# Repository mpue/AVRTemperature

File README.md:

AVRTemperature
==============================

Measuring temperature with the ATMega8 and a TSIC 0306. This version is interrupt driven.

Hardware: ATMega8/16MHz
 
This program measures the temperature of a TSIC0306 temperature sensor, which is
connected to the INT1 pin. The sensor itself is powered via the ZACPIN defined
in zacwire.h

At the beginning the TSIC is powered on and when the first falling edge occurs the measurement
starts. Timer 1 is started in normal mode. When the first rising edge occurs the timer is being
stopped and the value from the TCNT1 register is taken as strobe value.

From now on on each falling edge of the INT1 pin the timer1 is started in ctc mode. Each time
the OCR1A register is equal to the timer value, the TIMER1_COMPA_vect interrupt service routine
is being triggered. This is exactly the 50% duty cycle time which is needed to detect the state
of each bit.

After measuring the MSB the parity bit and the stop bit are being skipped, then the measurement
for the LSB continues, at the end the parity bit is skipped again and the measurement is complete.
The whole thing is driven by a "state machine" like mechanism. This in fact not a real state machine,
since we have no events, rules or transitions.
 
This code doesn't represent the most efficient solution. The goal was to understand the zacwire protocol
and to write human readable code. Feel free to improve the code and give suggestions.

Usage
==============================
You must have avrdude and avr-gcc installed. Use an ATMega8@16MHz, given the attached schematic.

Program with:

make program

You'll have to adjust your programmer before. Don't mess up the fuses!

Schematics and board layout resides in the eagle folder.

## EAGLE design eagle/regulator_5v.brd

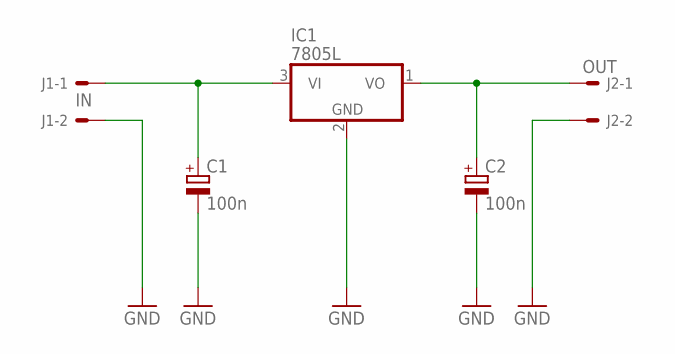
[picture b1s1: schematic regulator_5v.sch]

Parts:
C1, C2: 100n; TT2D5
IC1: 7805L; TO92
J1: IN; 6410-02
J2: OUT; 6410-02

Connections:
GND: C1.-, C2.-, IC1.2 (GND), J1.2, J2.2
unnamed: C1.+, IC1.3 (VI), J1.1
unnamed: C2.+, IC1.1 (VO), J2.1

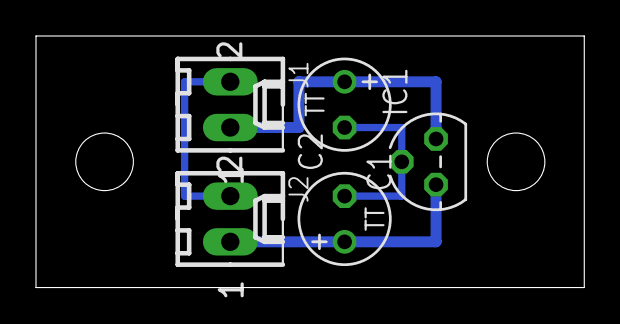
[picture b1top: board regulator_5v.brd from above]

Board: 2 copper layers, 30.5 x 14.0 mm, 5 parts (0 on the bottom side), 3 nets.

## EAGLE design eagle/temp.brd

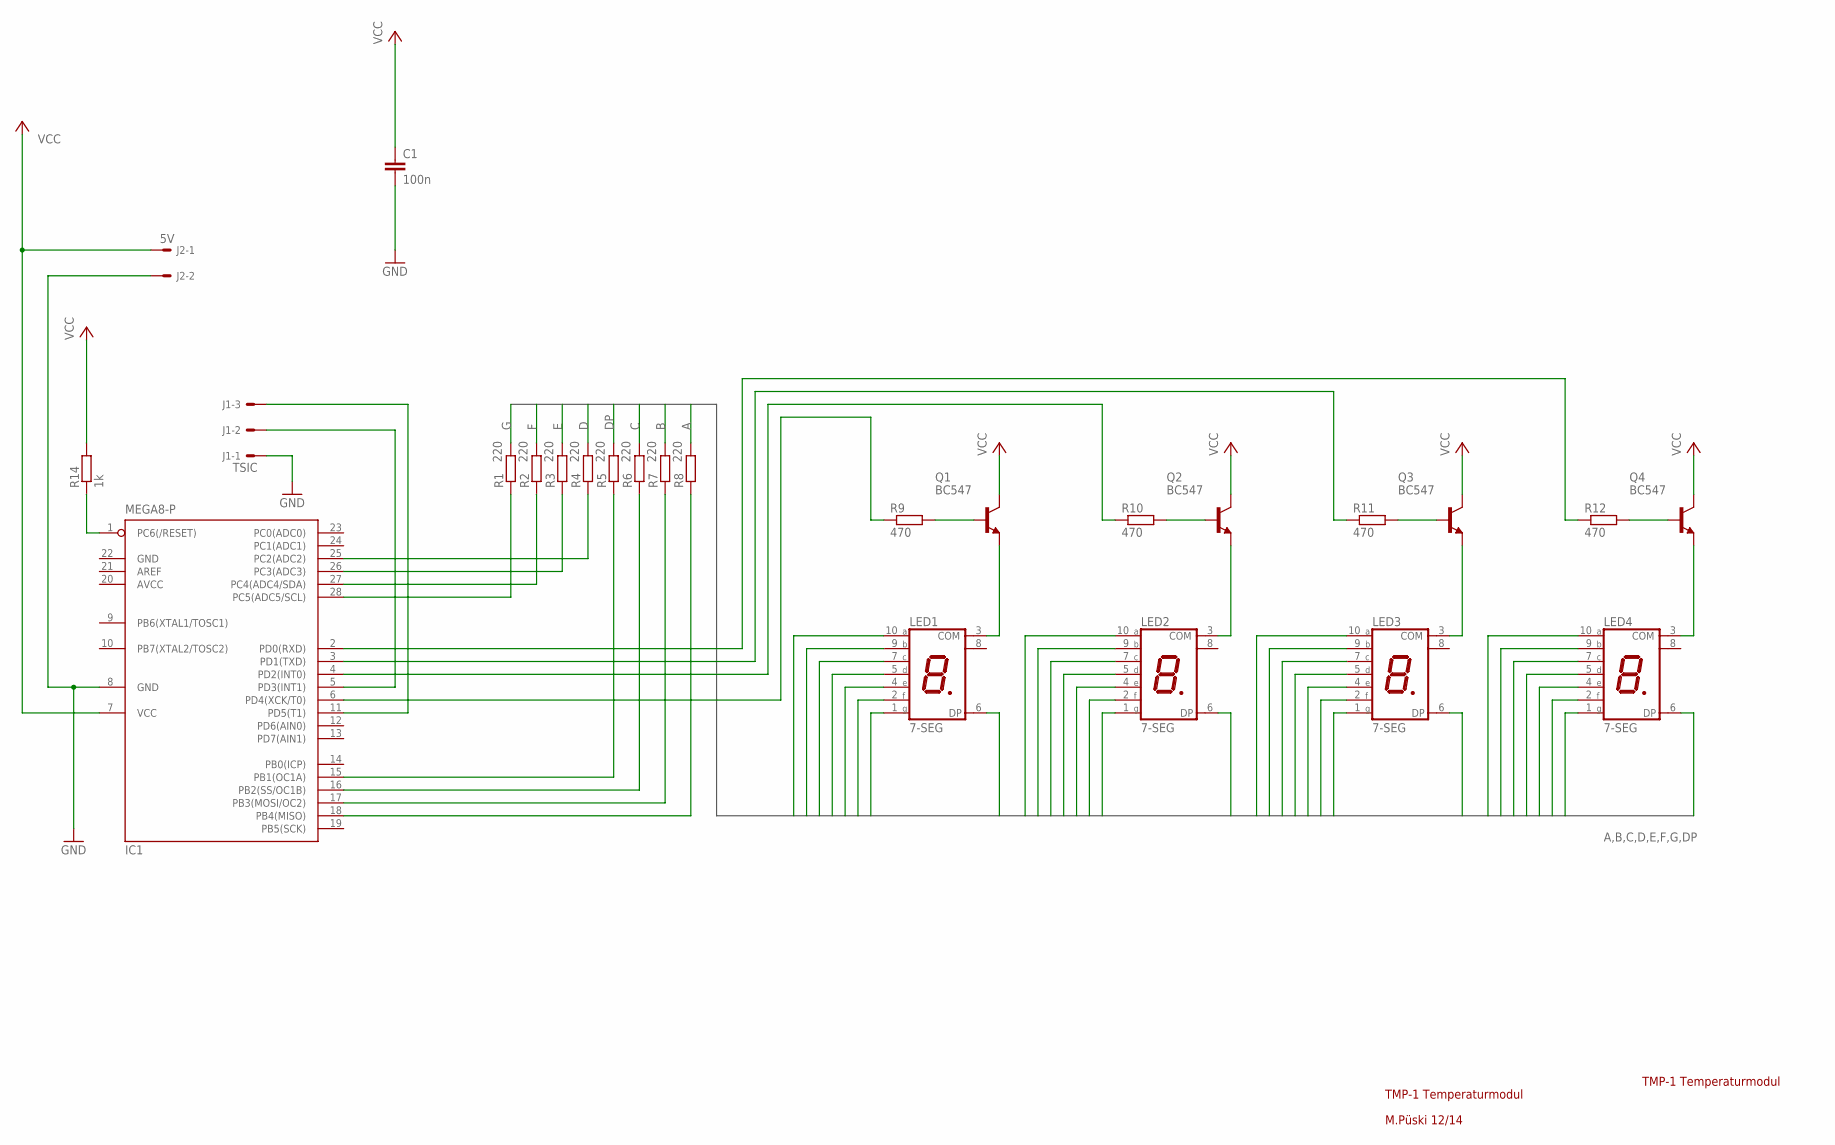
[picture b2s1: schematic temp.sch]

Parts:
C1: 100n; C050-024X044
IC1: MEGA8-P; DIL28-3
J1: TSIC; 6410-03
J2: 5V; 6410-02
LED1, LED2, LED3, LED4: 7-SEG; SA39-11SRWA
Q1, Q2, Q3, Q4: BC547; TO92
R1, R2, R4, R5, R6, R7, R8: 220; 0204/7
R3: 220; 0204V
R9, R10, R12: 470; 0204/7
R11: 470; 0204V
R14: 1k; 0204/7

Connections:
A: LED1.10 (A), LED2.10 (A), LED3.10 (A), LED4.10 (A), R8.2
AVCC: IC1.20 (AVCC)
B: LED1.9 (B), LED2.9 (B), LED3.9 (B), LED4.9 (B), R7.2
C: LED1.7 (C), LED2.7 (C), LED3.7 (C), LED4.7 (C), R6.2
D: LED1.5 (D), LED2.5 (D), LED3.5 (D), LED4.5 (D), R4.2
DP: LED1.6 (DP), LED2.6 (DP), LED3.6 (DP), LED4.6 (DP), R5.2
E: LED1.4 (E), LED2.4 (E), LED3.4 (E), LED4.4 (E), R3.2
F: LED1.2 (F), LED2.2 (F), LED3.2 (F), LED4.2 (F), R2.2
G: LED1.1 (G), LED2.1 (G), LED3.1 (G), LED4.1 (G), R1.2
GND: C1.2, IC1.8 (GND), IC1.22 (GND), J1.1, J2.2
unnamed: IC1.27 (PC4(ADC4/SDA)), R2.1
unnamed: IC1.26 (PC3(ADC3)), R3.1
unnamed: IC1.25 (PC2(ADC2)), R4.1
unnamed: IC1.15 (PB1(OC1A)), R5.1
unnamed: IC1.16 (PB2(SS/OC1B)), R6.1
unnamed: IC1.17 (PB3(MOSI/OC2)), R7.1
unnamed: IC1.18 (PB4(MISO)), R8.1
unnamed: Q1.2 (B), R9.2
unnamed: Q2.2 (B), R10.2
unnamed: Q3.2 (B), R11.2
unnamed: LED3.3 (COM), Q3.1 (E)
unnamed: LED2.3 (COM), Q2.1 (E)
unnamed: LED1.3 (COM), Q1.1 (E)
unnamed: IC1.2 (PD0(RXD)), R12.1
unnamed: IC1.3 (PD1(TXD)), R11.1
unnamed: IC1.4 (PD2(INT0)), R10.1
unnamed: IC1.28 (PC5(ADC5/SCL)), R1.1
unnamed: Q4.2 (B), R12.2
unnamed: LED4.3 (COM), Q4.1 (E)
unnamed: IC1.1 (PC6(/RESET)), R14.1
unnamed: IC1.6 (PD4(XCK/T0)), R9.1
unnamed: IC1.11 (PD5(T1)), J1.3
unnamed: IC1.5 (PD3(INT1)), J1.2
VCC: C1.1, IC1.7 (VCC), J2.1, Q1.3 (C), Q2.3 (C), Q3.3 (C), Q4.3 (C), R14.2

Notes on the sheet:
TMP-1 Temperaturmodul
M.Püski 12/14

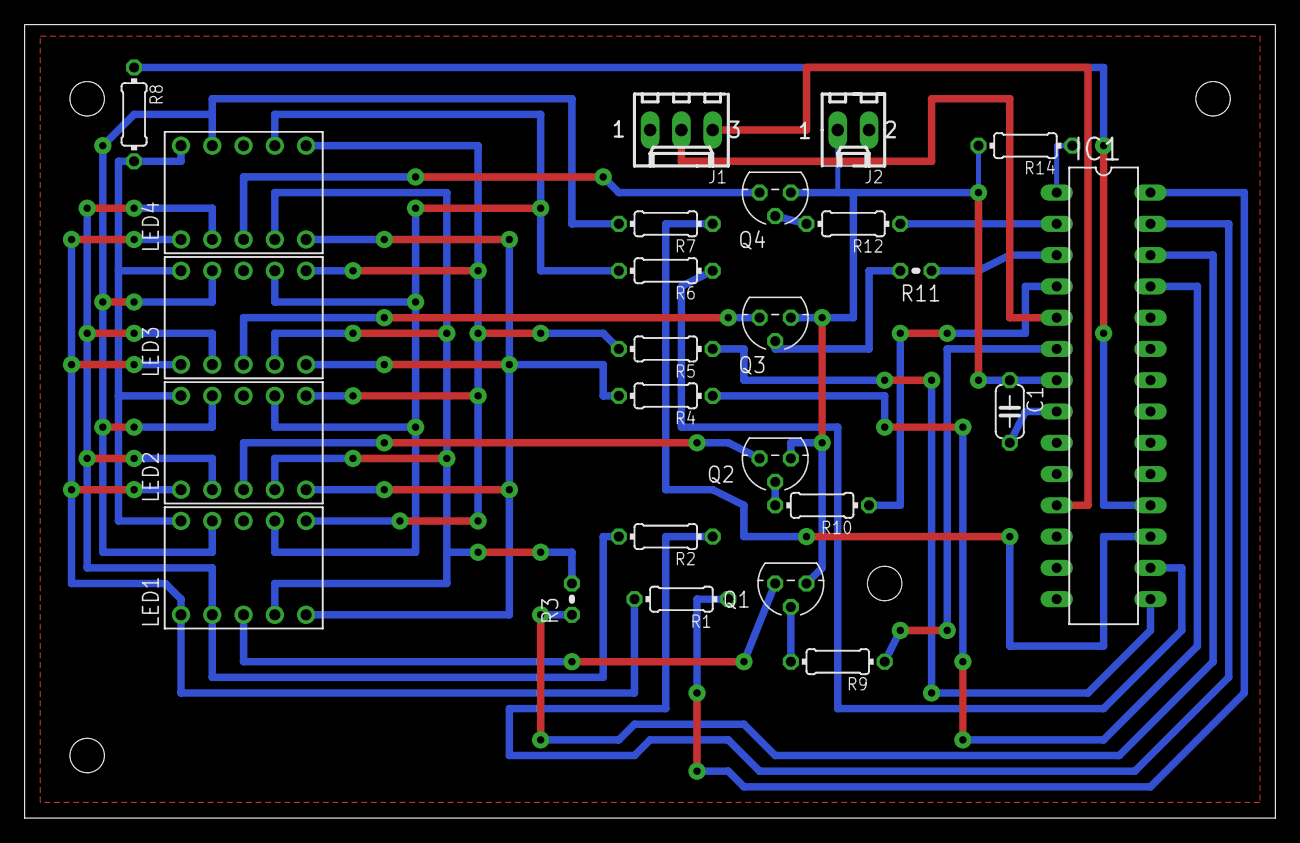
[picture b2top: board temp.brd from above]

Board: 2 copper layers, 101.6 x 64.4 mm, 25 parts (0 on the bottom side), 33 nets.
